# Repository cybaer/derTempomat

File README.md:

# derTempomat

Divider, Multiplier and Trigger Recorder for eurorack

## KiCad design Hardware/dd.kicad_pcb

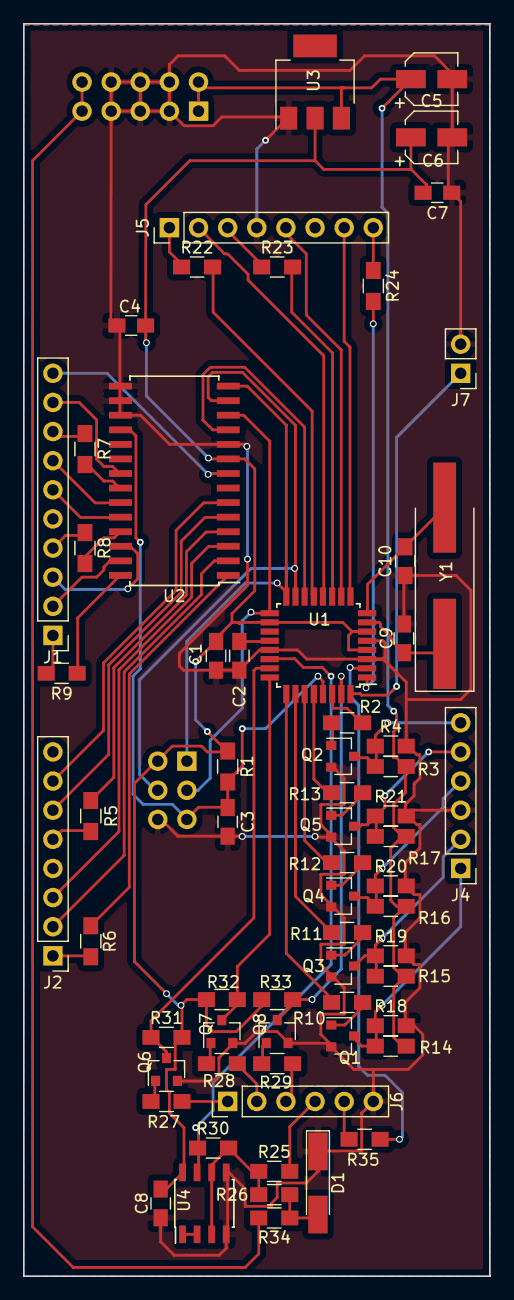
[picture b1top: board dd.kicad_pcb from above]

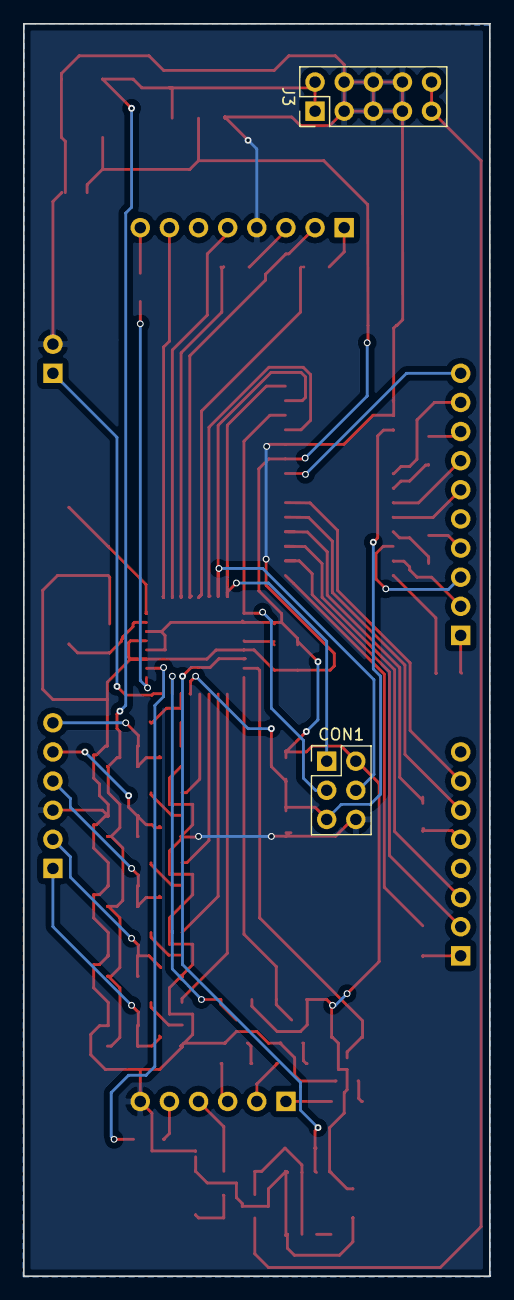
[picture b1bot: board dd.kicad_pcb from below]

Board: 2 copper layers, 40.6 x 109.2 mm, 67 parts (2 on the bottom side), 73 nets.

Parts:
C1, C2, C3, C4, C7, C8: 100n; C_0805_HandSoldering
C5, C6: 22µ; CP_Elec_4x5.3
C9, C10: 20p; C_0805_HandSoldering
CON1: AVR-ISP-6; Pin_Header_Straight_2x03_Pitch2.54mm
D1: 5V1; D_MiniMELF_Handsoldering
J1: Pin_Header_Straight_1x10_Pitch2.54mm
J2: Pin_Header_Straight_1x08_Pitch2.54mm
J3: Conn_02x05_Odd_Even; Pin_Header_Straight_2x05_Pitch2.54mm
J4, J6: Pin_Header_Straight_1x06_Pitch2.54mm
J5: Conn_01x08_Male; Pin_Header_Straight_1x08_Pitch2.54mm
J7: Conn_01x02_Male; Pin_Header_Straight_1x02_Pitch2.54mm
Q1, Q2, Q3, Q4, Q5, Q6, Q7, Q8: MMBT3904; SOT-23
R1, R2, R10, R11, R12, R13, R31, R32, R33: 10K; R_0805_HandSoldering
R3, R14, R15, R16, R17: 4K7; R_0805_HandSoldering
R4, R18, R19, R20, R21: 3K3; R_0805_HandSoldering
R5, R6, R7, R8, R9, R22, R23, R24, R35: 1K; R_0805_HandSoldering
R25, R26, R27, R28, R29, R30: 100K; R_0805_HandSoldering
R34: 5K; R_0805_HandSoldering
U1: ATMEGA328P-AU; TQFP-32_7x7mm_Pitch0.8mm
U2: MCP23S17; SOIC-28W_7.5x17.9mm_Pitch1.27mm
U3: LM1117-5.0; SOT-223
U4: MCP6002-xSN; SOIC-8_3.9x4.9mm_Pitch1.27mm
Y1: 20MHz; Crystal_SMD_HC49-SD_HandSoldering

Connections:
+12V: C5.1, J3.1, J3.2, R3.2, R14.2, R15.2, R16.2, R17.2, U3.3
-12VA: J3.9, J3.10, R34.2
-Ref: D1.2, R26.2, R34.1
/CV: R30.1, U1.22, U4.7
/Clk: Q6.3, R31.1, U1.23
/Debug: J7.1, U1.32
/LED1: R22.2, U1.13
/LED2: R23.2, U1.11
/LED3: R24.2, U1.1
/LED4: R35.2, U1.2
/Mod: Q8.3, R33.1, U1.31
/Rst: Q7.3, R32.1, U1.24
/T1: J5.2, U1.12
/T2: J5.5, U1.10
/T3: J5.7, U1.9
GND: C1.2, C2.2, C3.2, C4.2, C5.2, C6.2, C7.2, C8.2, C9.1, C10.1, CON1.6, D1.1, J3.3, J3.4, J3.5, J3.6, J3.7, J3.8, J4.3, J5.4, J6.6, J7.2, Q1.2, Q2.2, Q3.2, Q4.2, Q5.2, Q6.2, Q7.2, Q8.2, R4.2, R18.2, R19.2, R20.2, R21.2, U1.3, U1.5, U1.21, U2.10, U2.15, U2.16, U2.17, U3.1, U4.4, U4.5
unnamed: C2.1, U1.20
unnamed: C3.1, CON1.5, R1.2, U1.29, U2.18
unnamed: C9.2, U1.7, Y1.1
unnamed: C10.2, U1.8, Y1.2
unnamed: CON1.1, U1.16, U2.14
unnamed: CON1.3, U1.17, U2.12
unnamed: CON1.4, U1.15, U2.13
unnamed: J1.1, R9.1
unnamed: J1.2, U2.27
unnamed: J1.3, U2.26
unnamed: J1.4, R8.1
unnamed: J1.6, U2.24
unnamed: J1.7, U2.23
unnamed: J1.8, R7.1
unnamed: J1.9, U2.21
unnamed: J1.10, U2.8
unnamed: J2.1, R6.1
unnamed: J2.2, U2.2
unnamed: J2.3, U2.3
unnamed: J2.5, R5.1
unnamed: J2.6, U2.5
unnamed: J2.7, U2.6
unnamed: J4.1, Q1.3, R14.1, R18.1
unnamed: J4.2, Q3.3, R15.1, R19.1
unnamed: J4.4, Q4.3, R16.1, R20.1
unnamed: J4.5, Q5.3, R17.1, R21.1
unnamed: J4.6, Q2.3, R3.1, R4.1
unnamed: J5.1, R22.1
unnamed: J5.3, R23.1
unnamed: J5.8, R24.1
unnamed: J6.1, R27.2
unnamed: J6.2, R28.2
unnamed: J6.3, R29.2
unnamed: J6.4, R25.2
unnamed: J6.5, R35.1
unnamed: Q1.1, R10.1
unnamed: Q2.1, R2.1
unnamed: Q3.1, R11.1
unnamed: Q4.1, R12.1
unnamed: Q5.1, R13.1
unnamed: Q6.1, R27.1
unnamed: Q7.1, R28.1
unnamed: Q8.1, R29.1
unnamed: R2.2, U1.30
unnamed: R5.2, U2.4
unnamed: R6.2, U2.1
unnamed: R7.2, U2.22
unnamed: R8.2, U2.25
unnamed: R9.2, U2.28
unnamed: R10.2, U1.25
unnamed: R11.2, U1.26
unnamed: R12.2, U1.27
unnamed: R13.2, U1.28
unnamed: R25.1, R26.1, R30.2, U4.3, U4.6
unnamed: U1.14, U2.11
unnamed: U4.1, U4.2
VCC: C1.1, C4.1, C6.1, C7.1, C8.1, CON1.2, R1.1, R31.2, R32.2, R33.2, U1.4, U1.6, U1.18, U2.9, U3.2, U4.8

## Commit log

2018-07-16 Scheme and PCB added
2018-07-16 project start
2018-07-16 makefile added
2018-07-19 lib actualized
2018-07-19 .gitignore added
2018-07-22 LED4 added
2018-07-23 pins assigned
2018-07-25 change Mod from pin19 to 31, add debug
2018-07-29 new class StepControl
2018-08-01 some new ideas
2018-08-14 part references corrected
2018-09-26 footprint changed
2018-12-10 /lib actualized
2018-12-18 first HW test
2018-12-19 avrlib improved
2018-12-20 first try for clocking
2018-12-20 submodule change
2019-04-17 clock reworked
2019-04-24 new class Ui safe copy in clock
2019-04-25 poll() and doEvents() activated
2019-08-07 Test
2019-08-09 app added ui state machine added
2019-08-09 small changes
2019-08-09 avrlib changes
2020-06-30 many improvements
